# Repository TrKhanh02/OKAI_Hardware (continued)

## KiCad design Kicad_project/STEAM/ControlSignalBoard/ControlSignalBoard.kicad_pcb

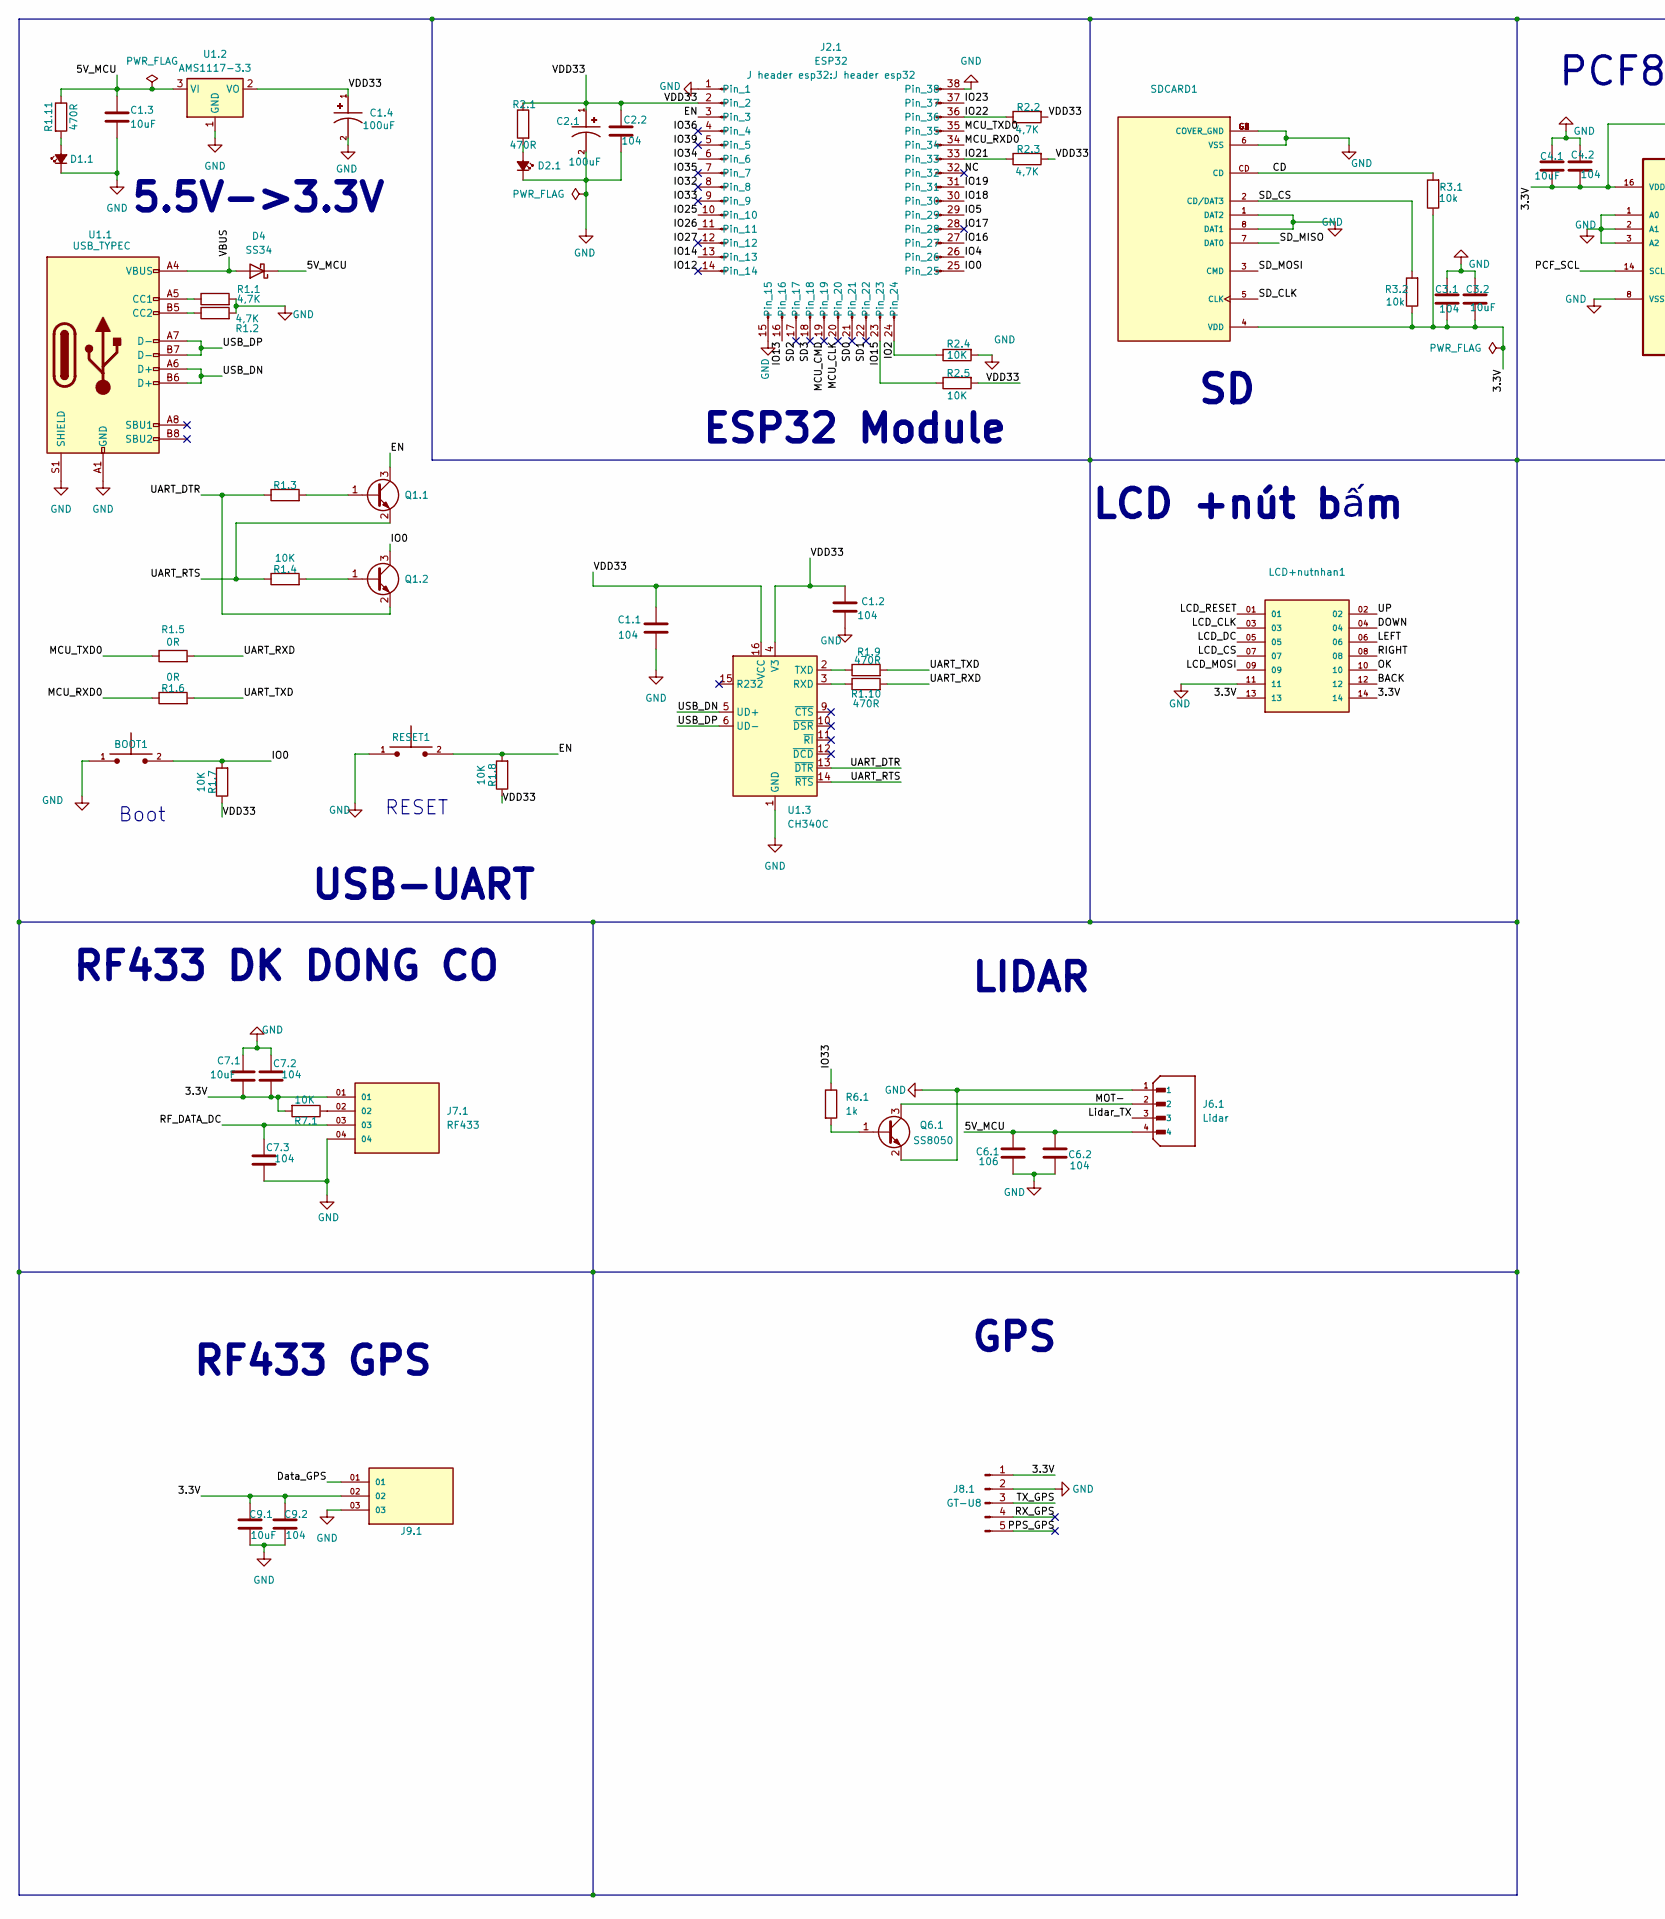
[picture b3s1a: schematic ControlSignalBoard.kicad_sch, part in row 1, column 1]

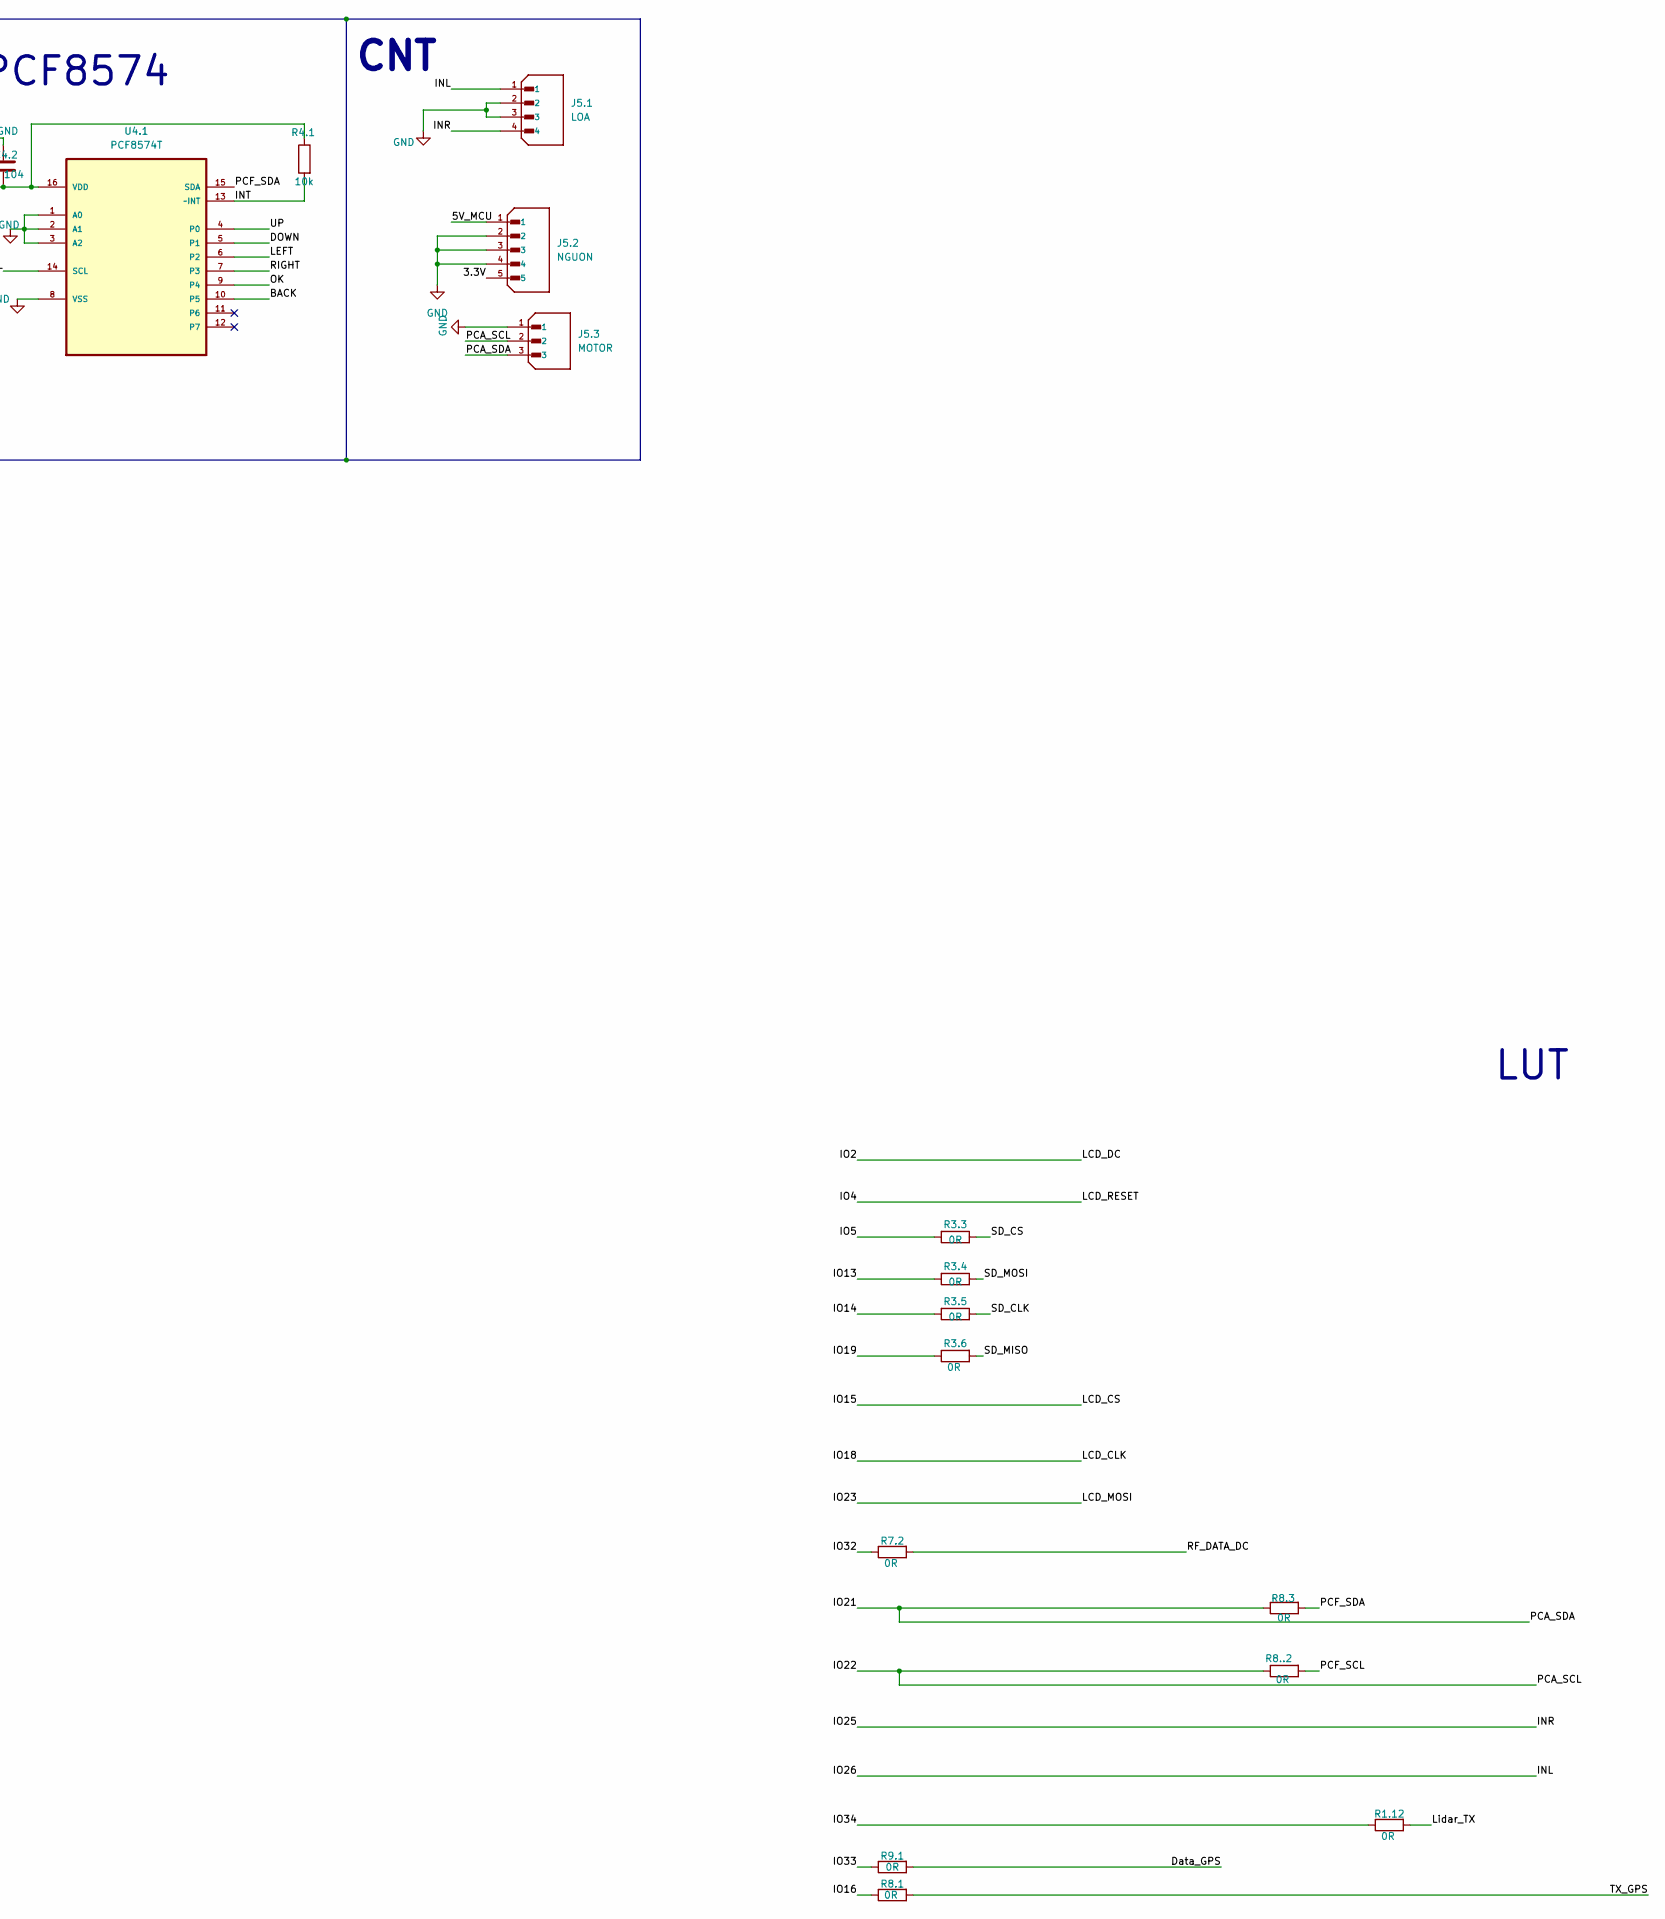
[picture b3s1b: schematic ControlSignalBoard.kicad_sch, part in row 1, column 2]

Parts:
BOOT1: TS10-63-26-BE-250-SMT-TR; SW_TS10-63-26-BE-250-SMT-TR; PARTREV 1.0
C1.1, C1.2, C2.2, C3.1, C4.2, C6.2, C7.2, C7.3, C9.2: 104; C_0805_2012Metric_Pad1.18x1.45mm_HandSolder
C1.3, C3.2, C4.1, C7.1, C9.1: 10uF; C_0805_2012Metric_Pad1.18x1.45mm_HandSolder
C1.4, C2.1: 100uF; CAPMP3216X180N; PARTREV 031320
C6.1: 106; C_0805_2012Metric_Pad1.18x1.45mm_HandSolder
D1.1, D2.1: LED_Small_Filled; LED_0805_2012Metric_Pad1.15x1.40mm_HandSolder
D4: SS34; D_SMA
J2.1: ESP32; J header esp32
J5.1: LOA; JST_B4B-XH-A_LF__SN_; PARTREV 7/4/21
J5.2: NGUON; JST_B5B-XH-A; PARTREV 7/4/21
J5.3: MOTOR; JST_B3B-XH-A; PARTREV 7/4/21
J6.1: Lidar; JST_B4B-XH-A_LF__SN_; PARTREV 7/4/21
J7.1: RF433; SAMTEC_MTSW-104-12-T-S-740; PARTREV R
J8.1: GT-U8; PinSocket_1x05_P2.54mm_Vertical
J9.1: RF_GPS; SAMTEC_MTSW-103-10-S-S-580; PARTREV R
LCD+nutnhan1: MTLW-107-07-G-D-230; SAMTEC_MTLW-107-07-G-D-230; PARTREV R
Q1.1, Q1.2, Q6.1: SS8050; SOT-23
R1.1, R1.2, R2.2, R2.3: 4,7K; R_0805_2012Metric_Pad1.20x1.40mm_HandSolder
R1.3, R1.4, R1.7, R1.8, R2.4, R2.5, R7.1: 10K; R_0805_2012Metric_Pad1.20x1.40mm_HandSolder
R1.5, R1.6, R1.12, R3.3, R3.4, R3.5, R3.6, R7.2, R8.1, R8.3, R8..2, R9.1: 0R; R_0805_2012Metric_Pad1.20x1.40mm_HandSolder
R1.9, R1.10, R1.11, R2.1: 470R; R_0805_2012Metric_Pad1.20x1.40mm_HandSolder
R3.1, R3.2, R4.1: 10k; R_0805_2012Metric_Pad1.20x1.40mm_HandSolder
R6.1: 1k; R_0805_2012Metric_Pad1.20x1.40mm_HandSolder
RESET1: TS10-63-26-BE-250-SMT-TR; SW_TS10-63-26-BE-250-SMT-TR; PARTREV 1.0
SDCARD1: MSD-1-A; CUI_MSD-1-A; PARTREV 1.0
U1.1: USB_TYPEC; USB_C_Receptacle_HRO_TYPE-C-31-M-12
U1.2: AMS1117-3.3; SOT-223-3_TabPin2
U1.3: CH340C; SOIC-16_3.9x9.9mm_P1.27mm
U4.1: PCF8574T; SOIC127P1032X265-16N; MPN PCF8574T

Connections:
/3.3V: C3.1.1, C3.2.1, C4.1.1, C4.2.1, C7.1.2, C7.2.2, C9.1.1, C9.2.1, J5.2.5, J7.1.01, J8.1.1, J9.1.02, LCD+nutnhan1.13, LCD+nutnhan1.14, R3.1.1, R3.2.1, R4.1.1, R7.1.2, SDCARD1.4 (VDD), U4.1.16 (VDD)
/5V_MCU: C1.3.1, C6.1.1, C6.2.1, D4.1 (K), J5.2.1, J6.1.4, R1.11.1, U1.2.3 (VI)
/BACK: LCD+nutnhan1.12, U4.1.10 (P5)
/CD: R3.1.2, SDCARD1.CD
/DOWN: LCD+nutnhan1.04, U4.1.5 (P1)
/Data_GPS: J9.1.01, R9.1.2
/EN: J2.1.3, Q1.1.3 (C), R1.8.2, RESET1.2
/INL: J2.1.11, J5.1.1
/INR: J2.1.10, J5.1.4
/INT: R4.1.2, U4.1.13 (~INT)
/IO0: BOOT1.2, J2.1.25, Q1.2.3 (C), R1.7.2
/IO2: J2.1.24, LCD+nutnhan1.05, R2.4.1
/IO4: J2.1.26, LCD+nutnhan1.01
/IO5: J2.1.29, R3.3.2
/IO12: J2.1.14
/IO13: J2.1.16, R3.4.2
/IO14: J2.1.13, R3.5.2
/IO15: J2.1.23, LCD+nutnhan1.07, R2.5.1
/IO16: J2.1.27, R8.1.1
/IO17: J2.1.28
/IO18: J2.1.30, LCD+nutnhan1.03
/IO19: J2.1.31, R3.6.1
/IO21: J2.1.33, J5.3.3, R2.3.1, R8.3.1
/IO22: J2.1.36, J5.3.2, R2.2.1, R8..2.1
/IO23: J2.1.37, LCD+nutnhan1.09
/IO27: J2.1.12
/IO32: J2.1.8, R7.2.1
/IO33: J2.1.9, R6.1.1, R9.1.1
/IO34: J2.1.6, R1.12.1
/IO35: J2.1.7
/IO36: J2.1.4
/IO39: J2.1.5
/LEFT: LCD+nutnhan1.06, U4.1.6 (P2)
/Lidar_TX: J6.1.3, R1.12.2
/MCU_CLK: J2.1.20
/MCU_CMD: J2.1.19
/MCU_RXD0: J2.1.34, R1.6.1
/MCU_TXD0: J2.1.35, R1.5.1
/MOT-: J6.1.2, Q6.1.3 (C)
/NC: J2.1.32
/OK: LCD+nutnhan1.10, U4.1.9 (P4)
/PCF_SCL: R8..2.2, U4.1.14 (SCL)
/PCF_SDA: R8.3.2, U4.1.15 (SDA)
/PPS_GPS: J8.1.5
/RF_DATA_DC: C7.3.1, J7.1.03, R7.2.2
/RIGHT: LCD+nutnhan1.08, U4.1.7 (P3)
/RX_GPS: J8.1.4
/SD0: J2.1.21
/SD1: J2.1.22
/SD2: J2.1.17
/SD3: J2.1.18
/SD_CLK: R3.5.1, SDCARD1.5 (CLK)
/SD_CS: R3.2.2, R3.3.1, SDCARD1.2 (CD/DAT3)
/SD_MISO: R3.6.2, SDCARD1.7 (DAT0)
/SD_MOSI: R3.4.1, SDCARD1.3 (CMD)
/TX_GPS: J8.1.3, R8.1.2
/UART_DTR: Q1.2.2 (E), R1.3.1, U1.3.13 (~DTR)
/UART_RTS: Q1.1.2 (E), R1.4.1, U1.3.14 (~RTS)
/UART_RXD: R1.5.2, R1.10.2
/UART_TXD: R1.6.2, R1.9.2
/UP: LCD+nutnhan1.02, U4.1.4 (P0)
/USB_DN: U1.1.A6 (D+), U1.1.B6 (D+), U1.3.5 (UD+)
/USB_DP: U1.1.A7 (D-), U1.1.B7 (D-), U1.3.6 (UD-)
/VBUS: D4.2 (A), U1.1.A4 (VBUS), U1.1.A9 (VBUS), U1.1.B4 (VBUS), U1.1.B9 (VBUS)
/VDD33: C1.1.2, C1.2.2, C1.4.1, C2.1.1, C2.2.1, J2.1.2, R1.7.1, R1.8.1, R2.1.1, R2.2.2, R2.3.2, R2.5.2, U1.2.2 (VO), U1.3.4 (V3), U1.3.16 (VCC)
GND: BOOT1.1, C1.1.1, C1.2.1, C1.3.2, C1.4.2, C2.1.2, C2.2.2, C3.1.2, C3.2.2, C4.1.2, C4.2.2, C6.1.2, C6.2.2, C7.1.1, C7.2.1, C7.3.2, C9.1.2, C9.2.2, D1.1.1 (K), D2.1.1 (K), J2.1.1, J2.1.15, J2.1.38, J2.1.39_1, J2.1.39_2, J2.1.39_3, J2.1.39_4, J2.1.39_5, J2.1.39_6, J2.1.39_7, J2.1.39_8, J2.1.39_9, J5.1.2, J5.1.3, J5.2.2, J5.2.3, J5.2.4, J5.3.1, J6.1.1, J7.1.04, J8.1.2, J9.1.03, LCD+nutnhan1.11, Q6.1.2 (E), R1.1.2, R1.2.2, R2.4.2, RESET1.1, SDCARD1.1 (DAT2), SDCARD1.6 (VSS), SDCARD1.8 (DAT1), SDCARD1.G1 (COVER_GND), SDCARD1.G2 (COVER_GND), SDCARD1.G3 (COVER_GND), SDCARD1.G4 (COVER_GND), U1.1.A1 (GND), U1.1.A12 (GND), U1.1.B1 (GND), U1.1.B12 (GND), U1.1.S1 (SHIELD), U1.2.1 (GND), U1.3.1 (GND), U4.1.1 (A0), U4.1.2 (A1), U4.1.3 (A2), U4.1.8 (VSS)
unnamed: D1.1.2 (A), R1.11.2
unnamed: D2.1.2 (A), R2.1.2
unnamed: J7.1.02, R7.1.1
unnamed: Q1.1.1 (B), R1.3.2
unnamed: Q1.2.1 (B), R1.4.2
unnamed: Q6.1.1 (B), R6.1.2
unnamed: R1.1.1, U1.1.A5 (CC1)
unnamed: R1.2.1, U1.1.B5 (CC2)
unnamed: R1.10.1, U1.3.3 (RXD)
unnamed: R1.9.1, U1.3.2 (TXD)

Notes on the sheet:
Boot
LIDAR
LCD +nút bấm
GPS
CNT
RESET
RF433 DK DONG CO
RF433 GPS
5.5V->3.3V
ESP32 Module
PCF8574
LUT
USB-UART

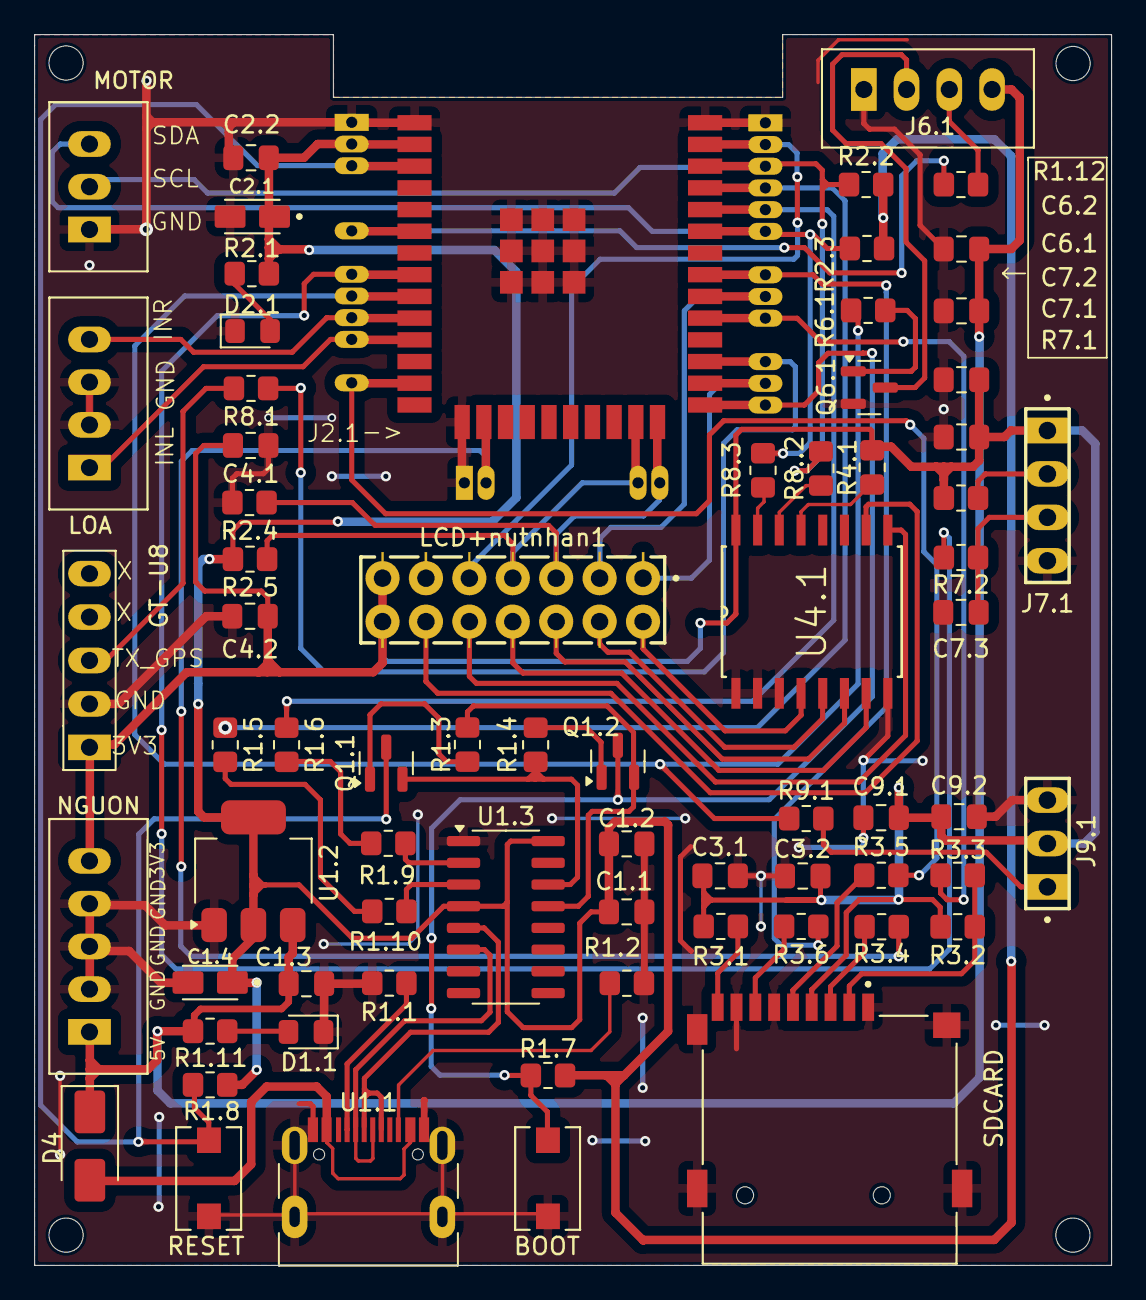
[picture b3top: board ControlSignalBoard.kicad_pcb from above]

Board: 2 copper layers, 63.0 x 72.0 mm, 70 parts (0 on the bottom side), 61 nets.

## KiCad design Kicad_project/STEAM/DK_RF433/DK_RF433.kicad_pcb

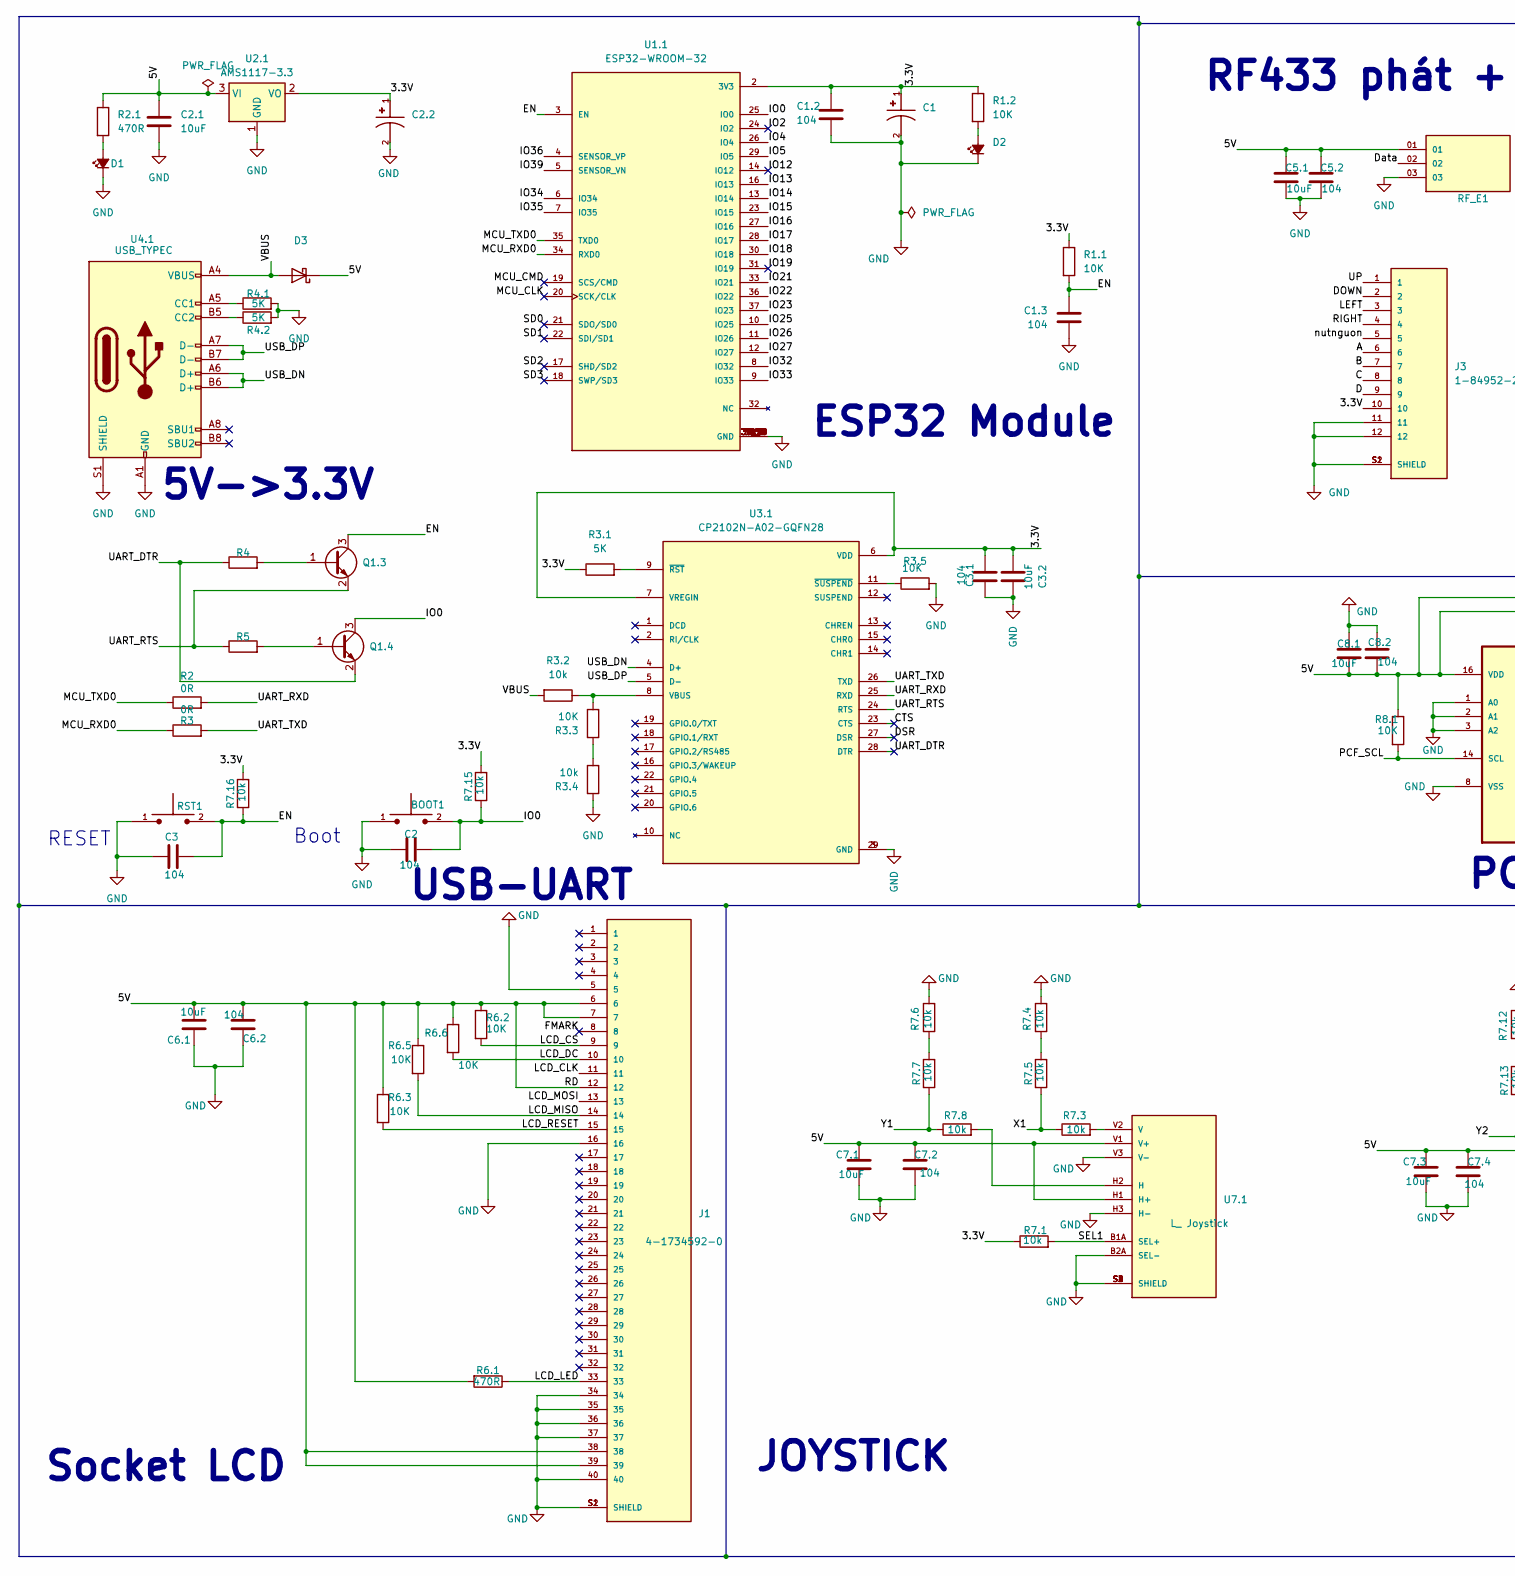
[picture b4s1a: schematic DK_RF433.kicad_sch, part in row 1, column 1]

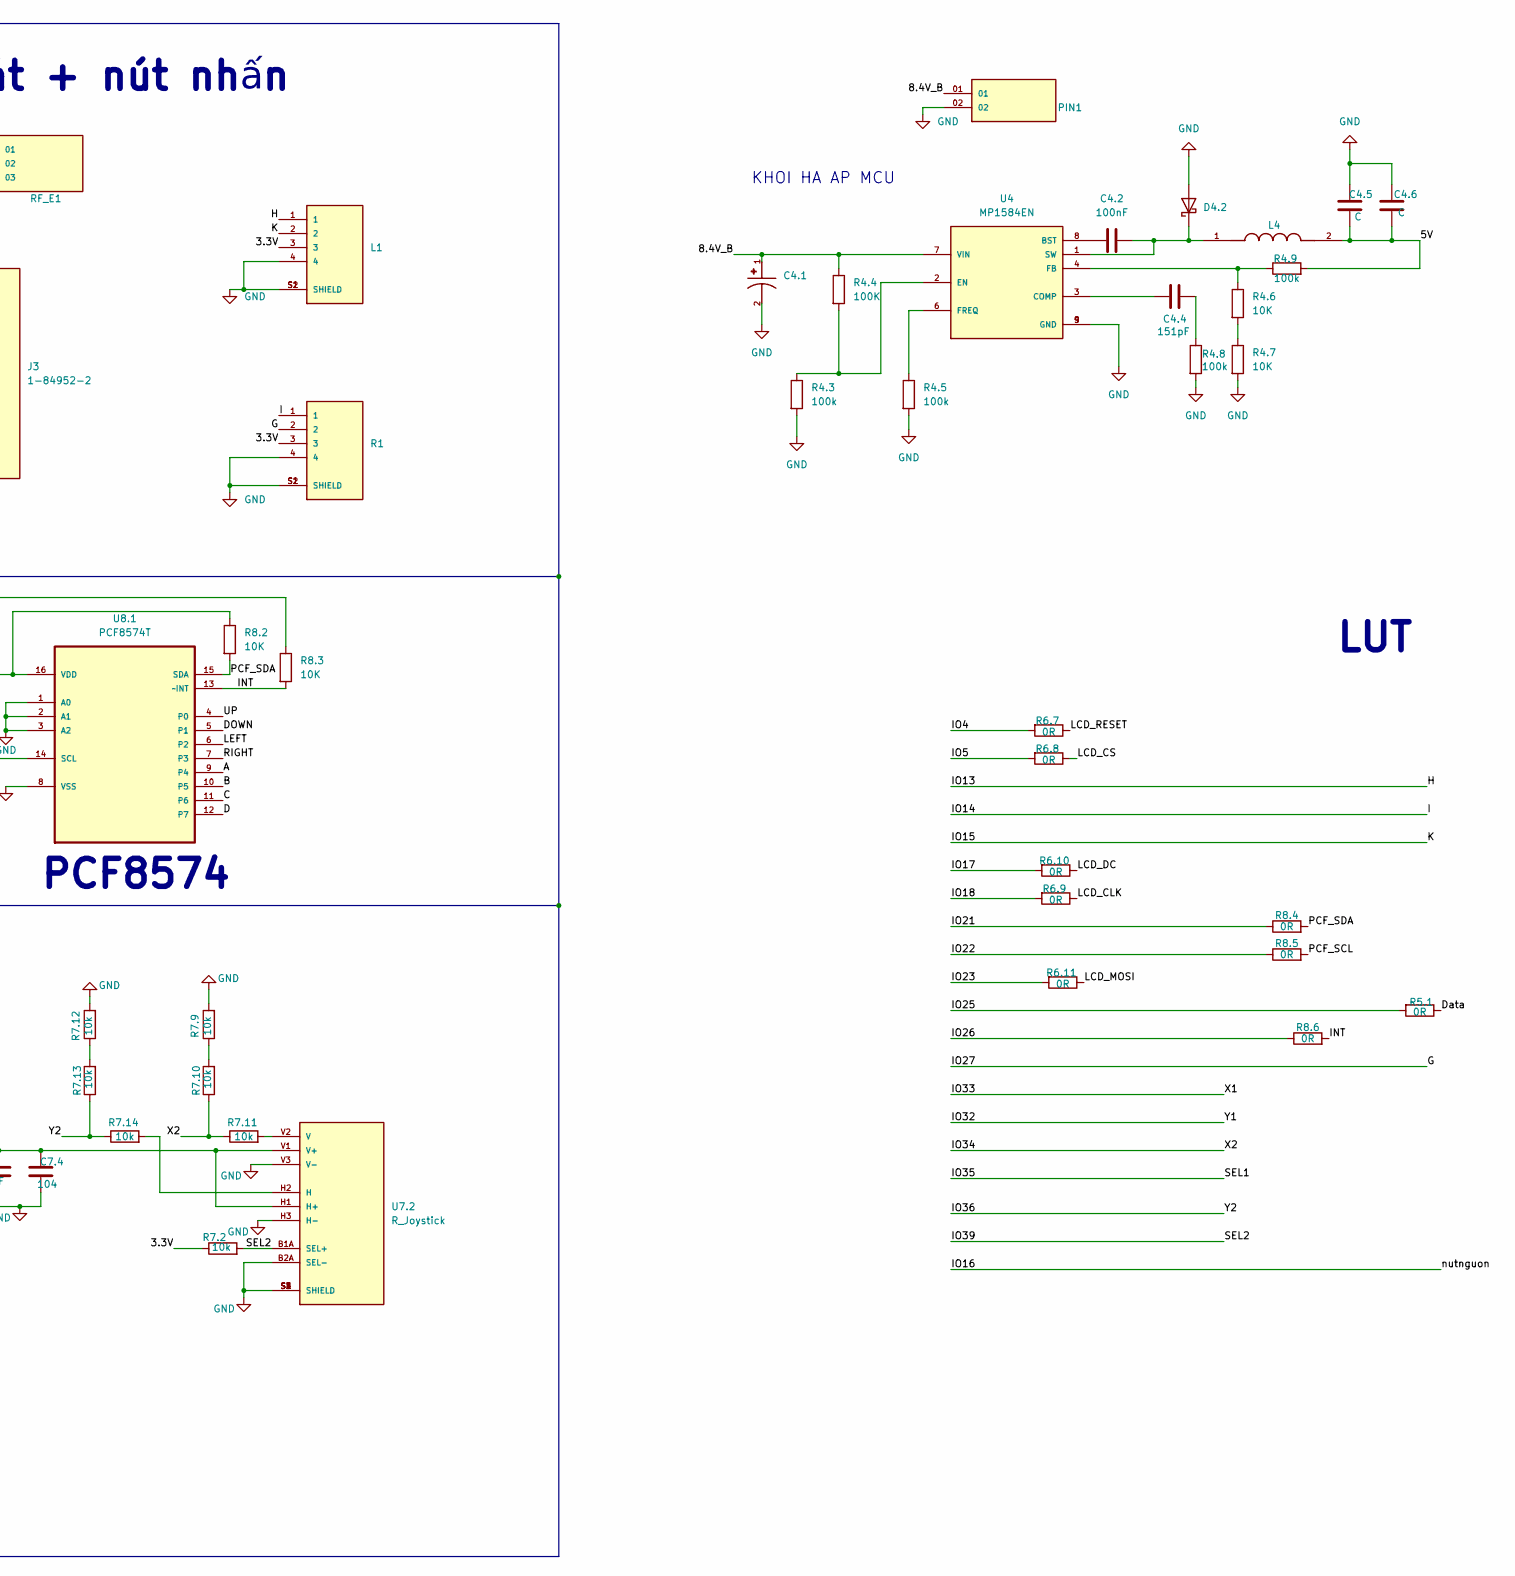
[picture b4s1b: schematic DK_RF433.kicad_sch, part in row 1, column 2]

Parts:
BOOT1: TS10-63-26-BE-250-SMT-TR; SW_TS10-63-26-BE-250-SMT-TR; PARTREV 1.0
C1, C4.1: TAJA106K016RNJ; CAPMP3216X180N; PARTREV 031320
C1.2, C1.3, C2, C3, C3.1, C5.2, C6.2, C7.2, C7.4, C8.2: 104; C_0805_2012Metric_Pad1.18x1.45mm_HandSolder
C2.1, C3.2, C5.1, C6.1, C7.1, C7.3, C8.1: 10uF; C_0805_2012Metric_Pad1.18x1.45mm_HandSolder
C2.2: 22uF; CAPMP3216X180N; PARTREV 031320
C4.2: 100nF; C_0805_2012Metric_Pad1.18x1.45mm_HandSolder
C4.4: 151pF; C_0805_2012Metric_Pad1.18x1.45mm_HandSolder
C4.5, C4.6: C; C_0805_2012Metric_Pad1.18x1.45mm_HandSolder
D1, D2: LED_Small_Filled; LED_0805_2012Metric_Pad1.15x1.40mm_HandSolder
D3: 1N5819WS; D_SOD-323_HandSoldering
D4.2: SS34; D_SMA
J1: 4-1734592-0; TE_4-1734592-0; PARTREV C; DigiKey_Part_Number A100226TR-ND
J3: 1-84952-2; TE_1-84952-2; PARTREV A4
L1: 84952-4; TE_84952-4; PARTREV A4
L4: SLF7032T-331MR22-2PF; IND_SLF7032T-331MR22-2PF; PARTREV N/A
PIN1: TSW-102-23-T-S; SAMTEC_TSW-102-23-T-S; PARTREV R
Q1.3, Q1.4: SS8050; SOT-23
R1: 84952-4; TE_84952-4; PARTREV A4
R1.1, R1.2, R3.3, R3.5, R4.6, R4.7, R6.2, R6.3, R6.5, R6.6, R8.1, R8.2, R8.3: 10K; R_0805_2012Metric_Pad1.20x1.40mm_HandSolder
R2, R3, R5.1, R6.7, R6.8, R6.9, R6.10, R6.11, R8.4, R8.5, R8.6: 0R; R_0805_2012Metric_Pad1.20x1.40mm_HandSolder
R2.1, R6.1: 470R; R_0805_2012Metric_Pad1.20x1.40mm_HandSolder
R3.1, R4.1, R4.2: 5K; R_0805_2012Metric_Pad1.20x1.40mm_HandSolder
R3.2, R3.4, R7.1, R7.2, R7.3, R7.4, R7.5, R7.6, R7.7, R7.8, R7.9, R7.10, R7.11, R7.12, R7.13, R7.14, R7.15, R7.16: 10k; R_0805_2012Metric_Pad1.20x1.40mm_HandSolder
R4, R5: R; R_0805_2012Metric_Pad1.20x1.40mm_HandSolder
R4.3, R4.5, R4.8, R4.9: 100k; R_0805_2012Metric_Pad1.20x1.40mm_HandSolder
R4.4: 100K; R_0805_2012Metric_Pad1.20x1.40mm_HandSolder
RF_E1: U5; SAMTEC_MTSW-103-10-S-S-580; PARTREV R
RST1: TS10-63-26-BE-250-SMT-TR; SW_TS10-63-26-BE-250-SMT-TR; PARTREV 1.0
U1.1: ESP32-WROOM-32; MODULE_ESP32-WROOM-32
U2.1: AMS1117-3.3; SOT-223-3_TabPin2
U3.1: CP2102N-A02-GQFN28; QFN50P500X500X80-29N; PARTREV 1.5
U4: MP1584EN; SOIC127P600X170-9N
U4.1: USB_TYPEC; USB_C_Receptacle_HRO_TYPE-C-31-M-12
U7.1: L_ Joystick; XDCR_COM-09032; PARTREV N/A
U7.2: R_Joystick; XDCR_COM-09032; PARTREV N/A
U8.1: PCF8574T; SOIC127P1032X265-16N; MPN PCF8574T

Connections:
/3.3V: C1.1, C1.2.1, C2.2.1, C3.1.2, C3.2.2, J3.10, L1.3, R1.3, R1.1.1, R1.2.1, R3.1.1, R7.1.1, R7.2.1, R7.15.2, R7.16.2, U1.1.2 (3V3), U2.1.2 (VO), U3.1.6 (VDD), U3.1.7 (VREGIN)
/5V: C2.1.1, C4.5.2, C4.6.2, C5.1.1, C5.2.1, C6.1.2, C6.2.2, C7.1.1, C7.2.1, C7.3.1, C7.4.1, C8.1.1, C8.2.1, D3.1 (K), J1.6, J1.7, J1.12, J1.38, J1.39, L4.2, R2.1.1, R4.9.2, R6.1.2, R6.2.1, R6.3.1, R6.5.1, R6.6.1, R8.1.1, R8.2.1, R8.3.1, RF_E1.01, U2.1.3 (VI), U7.1.H1 (H+), U7.1.V1 (V+), U7.2.H1 (H+), U7.2.V1 (V+), U8.1.16 (VDD)
/8.4V_B: C4.1.1, PIN1.01, R4.4.1, U4.7 (VIN)
/A: J3.6, U8.1.9 (P4)
/B: J3.7, U8.1.10 (P5)
/C: J3.8, U8.1.11 (P6)
/CTS: U3.1.23 (CTS)
/D: J3.9, U8.1.12 (P7)
/DOWN: J3.2, U8.1.5 (P1)
/DSR: U3.1.27 (DSR)
/Data: R5.1.1, RF_E1.02
/EN: C1.3.1, C3.2, Q1.3.3 (C), R1.1.2, R7.16.1, RST1.2, U1.1.3 (EN)
/FMARK: J1.8
/G: R1.2, U1.1.12 (IO27)
/H: L1.1, U1.1.16 (IO13)
/I: R1.1, U1.1.13 (IO14)
/INT: R8.3.2, R8.6.2, U8.1.13 (~INT)
/IO0: BOOT1.2, C2.2, Q1.4.3 (C), R7.15.1, U1.1.25 (IO0)
/IO2: U1.1.24 (IO2)
/IO4: R6.7.2, U1.1.26 (IO4)
/IO5: R6.8.2, U1.1.29 (IO5)
/IO12: U1.1.14 (IO12)
/IO15: L1.2, U1.1.23 (IO15)
/IO16: J3.5, U1.1.27 (IO16)
/IO17: R6.10.2, U1.1.28 (IO17)
/IO18: R6.9.2, U1.1.30 (IO18)
/IO19: U1.1.31 (IO19)
/IO21: R8.4.1, U1.1.33 (IO21)
/IO22: R8.5.1, U1.1.36 (IO22)
/IO23: R6.11.2, U1.1.37 (IO23)
/IO25: R5.1.2, U1.1.10 (IO25)
/IO26: R8.6.1, U1.1.11 (IO26)
/IO32: R7.7.1, R7.8.1, U1.1.8 (IO32)
/IO33: R7.3.1, R7.5.1, U1.1.9 (IO33)
/IO34: R7.10.1, R7.11.1, U1.1.6 (IO34)
/IO35: R7.1.2, U1.1.7 (IO35), U7.1.B1A (SEL+)
/IO36: R7.13.1, R7.14.1, U1.1.4 (SENSOR_VP)
/IO39: R7.2.2, U1.1.5 (SENSOR_VN), U7.2.B1A (SEL+)
/LCD_CLK: J1.11, R6.9.1
/LCD_CS: J1.9, R6.2.2, R6.8.1
/LCD_DC: J1.10, R6.6.2, R6.10.1
/LCD_LED: J1.33, R6.1.1
/LCD_MISO: J1.14, R6.5.2
/LCD_MOSI: J1.13, R6.11.1
/LCD_RESET: J1.15, R6.3.2, R6.7.1
/LEFT: J3.3, U8.1.6 (P2)
/MCU_CLK: U1.1.20 (SCK/CLK)
/MCU_CMD: U1.1.19 (SCS/CMD)
/MCU_RXD0: R3.1, U1.1.34 (RXD0)
/MCU_TXD0: R2.1, U1.1.35 (TXD0)
/PCF_SCL: R8.1.2, R8.5.2, U8.1.14 (SCL)
/PCF_SDA: R8.2.2, R8.4.2, U8.1.15 (SDA)
/RIGHT: J3.4, U8.1.7 (P3)
/SD0: U1.1.21 (SDO/SD0)
/SD1: U1.1.22 (SDI/SD1)
/SD2: U1.1.17 (SHD/SD2)
/SD3: U1.1.18 (SWP/SD3)
/UART_DTR: Q1.4.2 (E), R4.1, U3.1.28 (DTR)
/UART_RTS: Q1.3.2 (E), R5.1, U3.1.24 (RTS)
/UART_RXD: R2.2, U3.1.25 (RXD)
/UART_TXD: R3.2, U3.1.26 (TXD)
/UP: J3.1, U8.1.4 (P0)
/USB_DN: U3.1.4 (D+), U4.1.A6 (D+), U4.1.B6 (D+)
/USB_DP: U3.1.5 (D-), U4.1.A7 (D-), U4.1.B7 (D-)
/VBUS: D3.2 (A), R3.2.2, U4.1.A4 (VBUS), U4.1.A9 (VBUS), U4.1.B4 (VBUS), U4.1.B9 (VBUS)
GND: BOOT1.1, C1.2, C1.2.2, C1.3.2, C2.1, C2.1.2, C2.2.2, C3.1, C3.1.1, C3.2.1, C4.1.2, C4.5.1, C4.6.1, C5.1.2, C5.2.2, C6.1.1, C6.2.1, C7.1.2, C7.2.2, C7.3.2, C7.4.2, C8.1.2, C8.2.2, D1.1 (K), D2.1 (K), D4.2.2 (A), J1.5, J1.16, J1.34, J1.35, J1.36, J1.37, J1.40, J1.S1 (SHIELD), J1.S2 (SHIELD), J3.11, J3.12, J3.S1 (SHIELD), J3.S2 (SHIELD), L1.4, L1.S1 (SHIELD), L1.S2 (SHIELD), PIN1.02, R1.4, R1.S1 (SHIELD), R1.S2 (SHIELD), R3.4.1, R3.5.2, R4.1.2, R4.2.2, R4.3.2, R4.5.2, R4.7.2, R4.8.2, R7.4.2, R7.6.2, R7.9.2, R7.12.2, RF_E1.03, RST1.1, U1.1.1 (GND), U1.1.15 (GND), U1.1.38 (GND), U1.1.39_1 (GND), U1.1.39_2 (GND), U1.1.39_3 (GND), U1.1.39_4 (GND), U1.1.39_5 (GND), U1.1.39_6 (GND), U1.1.39_7 (GND), U1.1.39_8 (GND), U1.1.39_9 (GND), U1.1.39_10 (GND), U1.1.39_11 (GND), U1.1.39_12 (GND), U1.1.39_13 (GND), U1.1.39_14 (GND), U1.1.39_15 (GND), U1.1.39_16 (GND), U1.1.39_17 (GND), U1.1.39_18 (GND), U1.1.39_19 (GND), U1.1.39_20 (GND), U1.1.39_21 (GND), U2.1.1 (GND), U3.1.3 (GND), U3.1.29 (GND), U4.5 (GND), U4.9 (GND), U4.1.A1 (GND), U4.1.A12 (GND), U4.1.B1 (GND), U4.1.B12 (GND), U4.1.S1 (SHIELD), U7.1.B2A (SEL-), U7.1.H3 (H-), U7.1.S1 (SHIELD), U7.1.S2 (SHIELD), U7.1.S3 (SHIELD), U7.1.S4 (SHIELD), U7.1.V3 (V-), U7.2.B2A (SEL-), U7.2.H3 (H-), U7.2.S1 (SHIELD), U7.2.S2 (SHIELD), U7.2.S3 (SHIELD), U7.2.S4 (SHIELD), U7.2.V3 (V-), U8.1.1 (A0), U8.1.2 (A1), U8.1.3 (A2), U8.1.8 (VSS)
unnamed: C4.4.2, R4.8.1
unnamed: D1.2 (A), R2.1.2
unnamed: D2.2 (A), R1.2.2
unnamed: C4.2.2, D4.2.1 (K), L4.1, U4.1 (SW)
unnamed: Q1.3.1 (B), R4.2
unnamed: Q1.4.1 (B), R5.2
unnamed: R3.3.1, R3.4.2
unnamed: R4.6.2, R4.7.1
unnamed: R7.4.1, R7.5.2
unnamed: R7.6.1, R7.7.2
unnamed: R7.9.1, R7.10.2
unnamed: R7.12.1, R7.13.2
unnamed: R3.2.1, R3.3.2, U3.1.8 (VBUS)
unnamed: R3.1.2, U3.1.9 (~RST)
unnamed: R3.5.1, U3.1.11 (~SUSPEND)
unnamed: C4.2.1, U4.8 (BST)
unnamed: C4.4.1, U4.3 (COMP)
unnamed: R4.3.1, R4.4.2, U4.2 (EN)
unnamed: R4.6.1, R4.9.1, U4.4 (FB)
unnamed: R4.5.1, U4.6 (FREQ)
unnamed: R4.1.1, U4.1.A5 (CC1)
unnamed: R4.2.1, U4.1.B5 (CC2)
unnamed: R7.8.2, U7.1.H2 (H)
unnamed: R7.3.2, U7.1.V2 (V)
unnamed: R7.14.2, U7.2.H2 (H)
unnamed: R7.11.2, U7.2.V2 (V)

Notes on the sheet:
USB-UART
5V->3.3V
ESP32 Module
Boot
PCF8574
KHOI HA AP MCU
LUT
JOYSTICK
RF433 phát + nút nhấn
Socket LCD
RESET

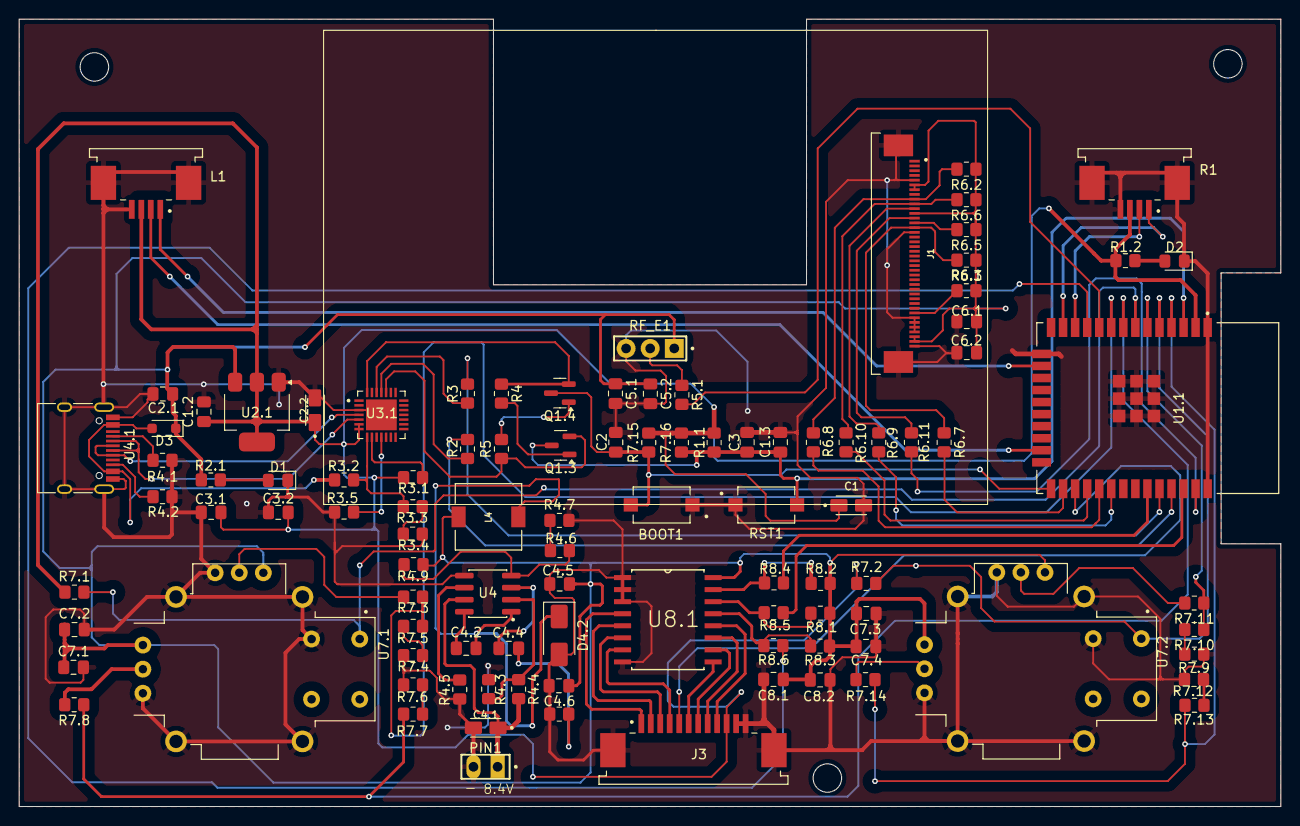
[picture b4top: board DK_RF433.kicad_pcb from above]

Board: 2 copper layers, 133.0 x 83.0 mm, 101 parts (0 on the bottom side), 80 nets.
